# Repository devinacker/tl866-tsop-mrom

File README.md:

This is a series of adapter boards designed to allow reading 16-bit TSOP48 mask ROMs using a TL866-series programmer. These ROMs have a pinout which is not compatible with the standard pinout used by TSOP48 EPROM/flash chips, and can be identified by pin 1 (/BYTE) being tied to either Vcc or ground. Sometimes these ROMs are manufactured with reverse pinouts (pins 1-24 on the right); this set of adapters is designed for both normal and reverse pinouts.

The adapters fit onto the same SN001 expansion board used for the regular SOP/TSOP adapters, and allow reading the chips as the corresponding 29-series flash chips (e.g. 29F800). ROM sizes from 8 to 64 Mbit are supported.

The following configurations are available:
* TL8-MT: normal pinout
* TL8-MTR: reverse pinout
* TL8-MTS: normal pinout, ZIF socket
* TL8-MTSR: reverse pinout, ZIF socket

Solder pads on the socket-less adapters are elongated to support both 16.4mm and 18.4mm chips.

Zipped gerbers are available from the releases section.

# Notes

* When reading, disable "Check ID" as this option is not supported by mask ROMs.
* If Pin Detect is enabled, the programmer will report errors on pins 11, 12, and 15, which are flash programming pins that don't exist on mask ROMs. If no other pins report errors, you can safely disable pin detection.
    * Pin 47 (/BYTE) may also display an error on mask ROMs that don't support byte mode - check your ROM's datasheet. The programmer should still use word mode when reading.
* The resistor R1 is a pulldown on A21, which is a ground pin on ROMs smaller than 64 Mbit. If you only plan on reading smaller ROMs, you can also use a 0-ohm or small wire jumper here.

# Parts

| Ref | Part |
| --- | --- |
| J1, J2 | 2x12 female pin header, 2.54mm pitch |
| R1 | 1206, 3.3k
| U1 | ANDK TSOP48-0.5-OTS04 (socketed boards only) |

# Board images

# License

These PCBs are released under the Creative Commons Attribution-ShareAlike 4.0 (CC BY-SA) license.

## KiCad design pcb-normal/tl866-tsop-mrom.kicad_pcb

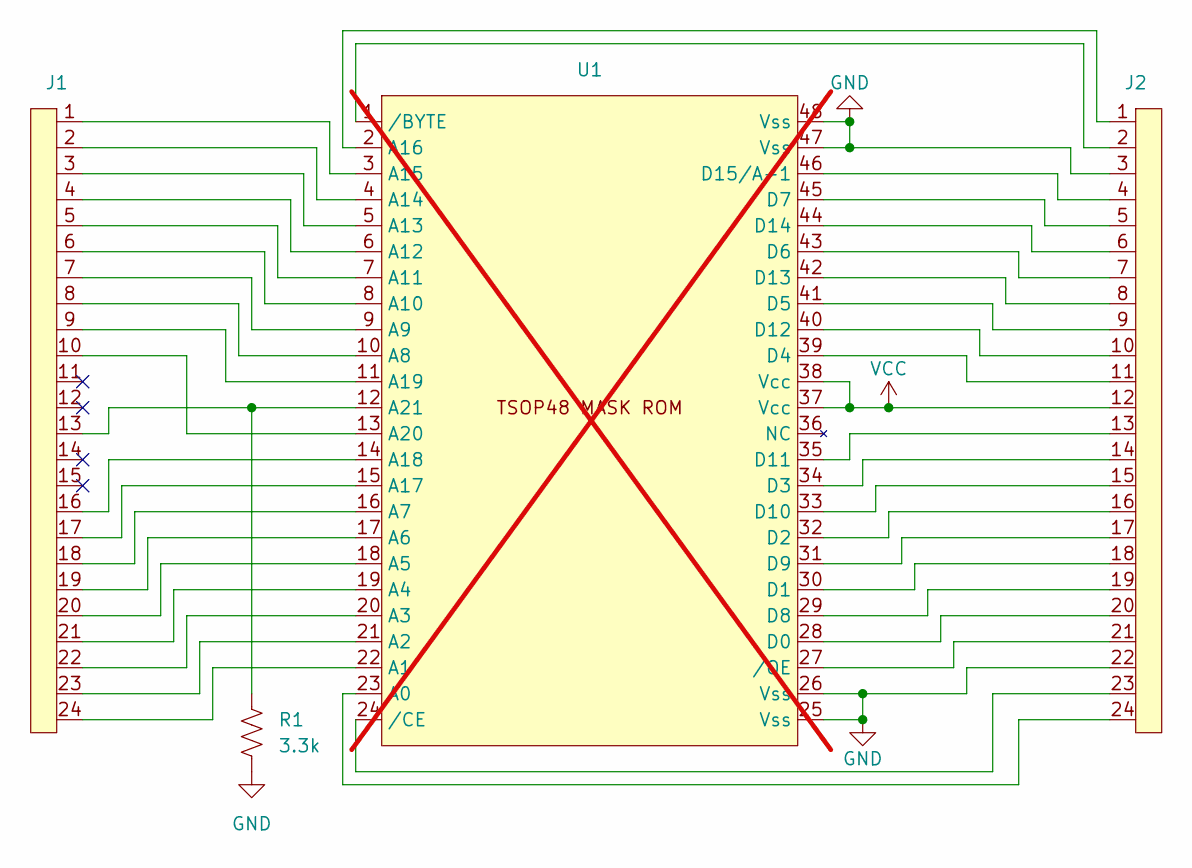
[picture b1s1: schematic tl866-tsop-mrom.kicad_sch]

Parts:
J1, J2: PinSocket_2x12_P2.54mm_Vertical
R1: 3.3k; R_1206_3216Metric_Pad1.30x1.75mm_HandSolder
U1: TSOP-I-48_16.4x12mm_ext; not fitted

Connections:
GND: J2.3, J2.22, R1.2, U1.25 (Vss), U1.26 (Vss), U1.47 (Vss), U1.48 (Vss)
unnamed: J2.24, U1.23 (A0)
unnamed: J1.24, U1.22 (A1)
unnamed: J1.23, U1.21 (A2)
unnamed: J1.22, U1.20 (A3)
unnamed: J1.21, U1.19 (A4)
unnamed: J1.20, U1.18 (A5)
unnamed: J1.19, U1.17 (A6)
unnamed: J1.18, U1.16 (A7)
unnamed: J1.8, U1.10 (A8)
unnamed: J1.7, U1.9 (A9)
unnamed: J1.6, U1.8 (A10)
unnamed: J1.5, U1.7 (A11)
unnamed: J1.4, U1.6 (A12)
unnamed: J1.3, U1.5 (A13)
unnamed: J1.2, U1.4 (A14)
unnamed: J1.1, U1.3 (A15)
unnamed: J2.1, U1.2 (A16)
unnamed: J1.17, U1.15 (A17)
unnamed: J1.16, U1.14 (A18)
unnamed: J1.9, U1.11 (A19)
unnamed: J1.10, U1.13 (A20)
unnamed: J1.13, R1.1, U1.12 (A21)
unnamed: J2.20, U1.28 (D0)
unnamed: J2.18, U1.30 (D1)
unnamed: J2.16, U1.32 (D2)
unnamed: J2.14, U1.34 (D3)
unnamed: J2.11, U1.39 (D4)
unnamed: J2.9, U1.41 (D5)
unnamed: J2.7, U1.43 (D6)
unnamed: J2.5, U1.45 (D7)
unnamed: J2.19, U1.29 (D8)
unnamed: J2.17, U1.31 (D9)
unnamed: J2.15, U1.33 (D10)
unnamed: J2.13, U1.35 (D11)
unnamed: J2.10, U1.40 (D12)
unnamed: J2.8, U1.42 (D13)
unnamed: J2.6, U1.44 (D14)
unnamed: J2.4, U1.46 (D15/A-1)
unnamed: J2.2, U1.1 (/BYTE)
unnamed: J2.23, U1.24 (/CE)
unnamed: J2.21, U1.27 (/OE)
VCC: J2.12, U1.37 (Vcc), U1.38 (Vcc)

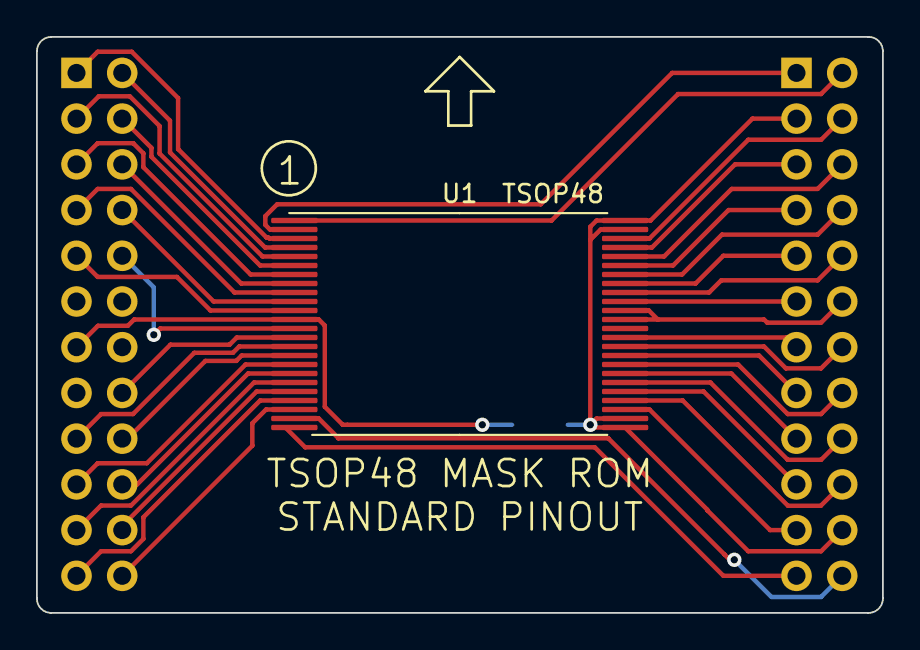
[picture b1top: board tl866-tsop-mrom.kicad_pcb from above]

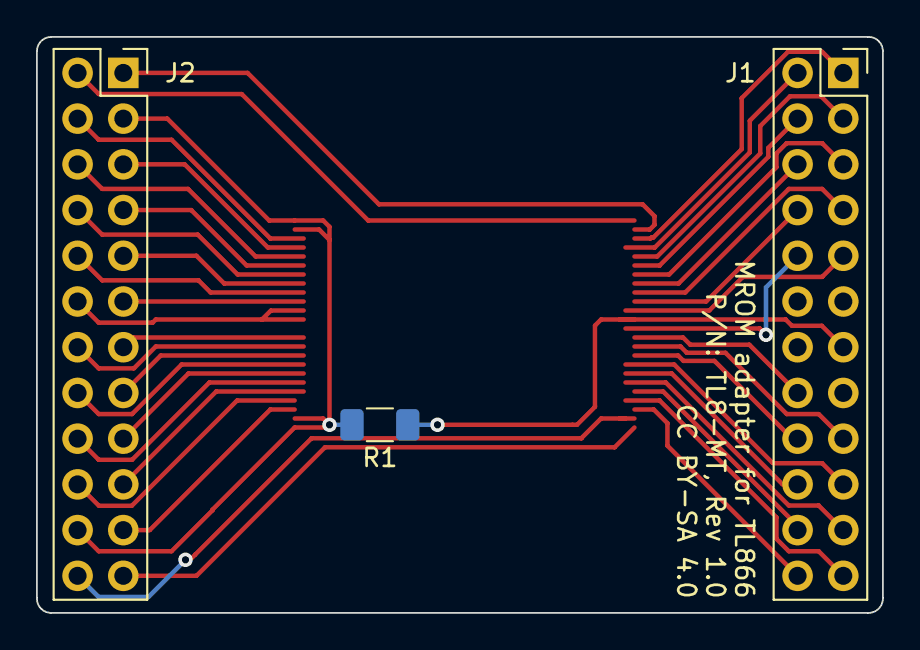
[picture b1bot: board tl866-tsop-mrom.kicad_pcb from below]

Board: 2 copper layers, 47.0 x 32.0 mm, 4 parts (3 on the bottom side), 43 nets.

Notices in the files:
pcb-normal/tl866-tsop-mrom.kicad_pcb:
CC BY-SA 4.0
